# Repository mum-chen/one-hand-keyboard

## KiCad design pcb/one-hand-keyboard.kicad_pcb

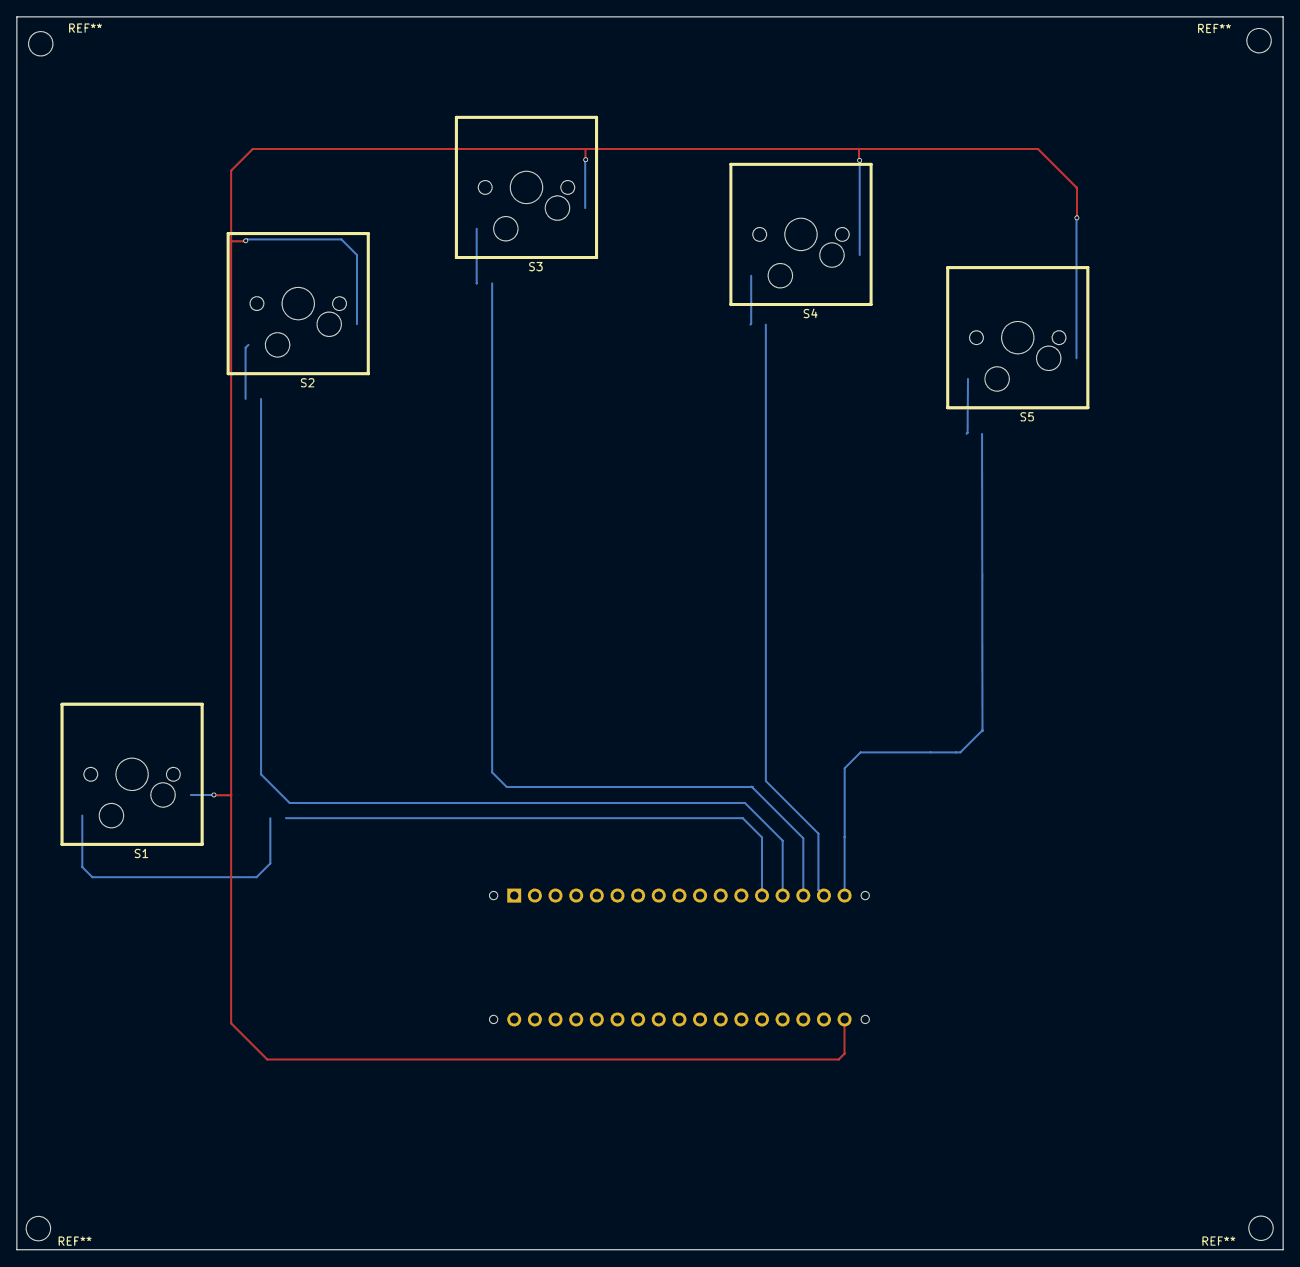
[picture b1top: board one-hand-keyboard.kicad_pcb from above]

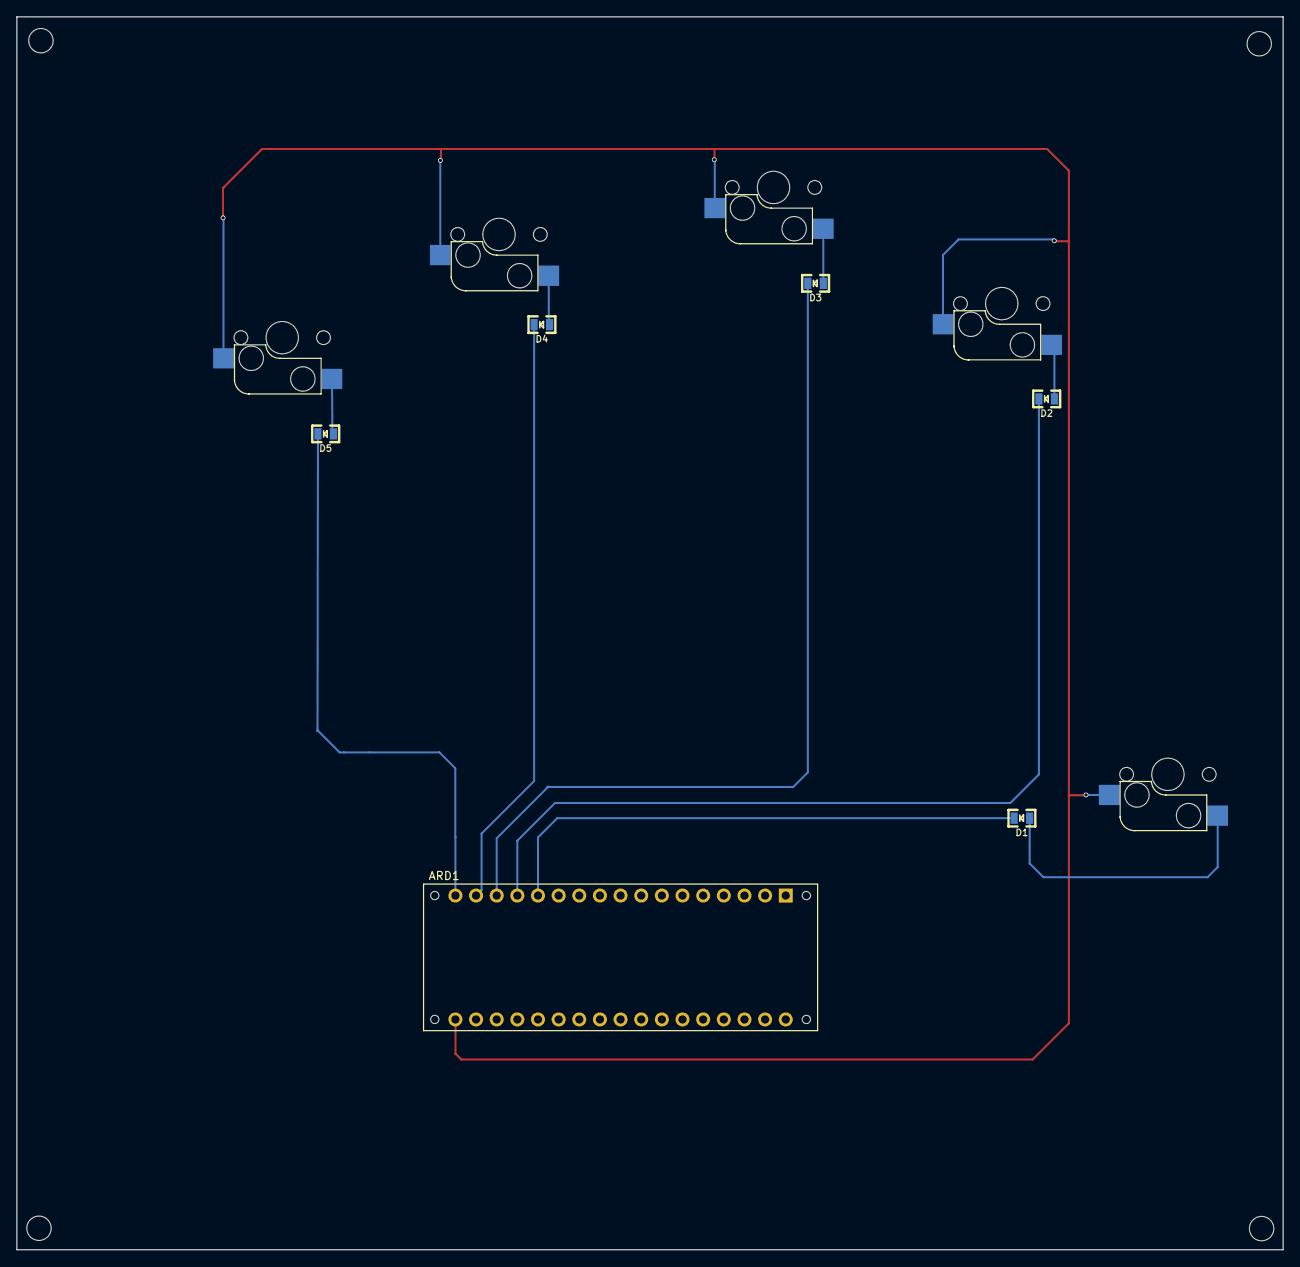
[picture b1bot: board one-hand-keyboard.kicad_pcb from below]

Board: 2 copper layers, 155.8 x 151.7 mm, 11 parts (6 on the bottom side), 11 nets.

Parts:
ARD1: Arduino_Micro_Socket
D1, D2, D3, D4, D5: 1N4148; 0805D
S1, S2, S3, S4, S5: MX1A; Key_Contact_MX1A

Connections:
/col1: ARD1.D8, D1.2
/col2: ARD1.D9, D2.2
/col3: ARD1.D10, D3.2
/col4: ARD1.D11, D4.2
/col5: ARD1.D12, D5.2
/row1: ARD1.D13, S1.1, S2.1, S3.1, S4.1, S5.1
unnamed: D1.1, S1.2
unnamed: D2.1, S2.2
unnamed: D3.1, S3.2
unnamed: D4.1, S4.2
unnamed: D5.1, S5.2

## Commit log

2018-04-07 feat(pcb): init
2018-04-07 feat(code): init
    - Check if the button is pressed in loop.
